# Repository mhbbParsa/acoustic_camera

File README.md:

# Acoustic Camera

https://github.com/user-attachments/assets/35040632-333c-4387-a5bf-bf2f547ff368

A real-time acoustic camera built around a 30-element MEMS microphone array and an FPGA beamformer. The FPGA extracts a single target frequency from every microphone, steers a 32×32 grid of look directions with a CORDIC-based phase rotator, and streams the resulting sound-power map out over UART to a Python viewer with either a plain live heatmap, or overlaid on a webcam feed. A physical switch flips the beamformer between a wide 180° field of view and a zoomed-in 60° view, another five switches set display gain (read back on the board's own 7-segment display), and holding spacebar in the camera overlay re-centers the heatmap on whatever's currently loudest.

Curiosity about phased array radar antennas and electronic beam steering led me to make this more accessible alternative, that replaces the difficult, expensive RF design with acoustic equivalents that are cheap to prototype and safe to probe by hand. The underlying math is identical. Only the wavelength and the hardware changed.

| | |
|---|---|
| Target frequency | 20 kHz (single-bin Goertzel) |
| Array | 30 mics, Fermat/Vogel spiral, ~90 mm diameter (measured from PCB layout) |
| Sample rates | 2 MHz PDM → 62.5 kHz decimated audio (2 MHz / 32) |
| Field of view | 60° (zoomed) or 180° (wide), switch-selectable |
| Angular resolution | ≈11° (rough λ/D estimate at 20 kHz, not a precise figure) |
| Frame rate to host | ≈60 fps (Goertzel-gated, comfortably clears the 2 Mbaud UART link) |
| FPGA | Xilinx Artix-7 `xc7a35tcpg236-1` (Digilent Basys3) |

*20 kHz source → 30-mic PCB → Pmod → Basys3 → USB → host PC live viewer.*

## How it works

```mermaid
flowchart TD
    MIC["30x SPH0641LU4H\nPDM MEMS mics"] -->|"30x 1-bit PDM"| MM["master_mic.sv\nclock gen + time-multiplexed capture"]
    MM -->|"mic_clk"| MIC
    MM -->|"30x PDM"| CIC["CIC.sv\n4th-order CIC decimation"]
    CIC -->|"30x 18-bit PCM"| GZ["goertzel.sv\nsingle-bin DFT @ target freq"]
    GZ -->|"30x (I,Q) phasors"| BF["beamformer.sv\nCORDIC delay-and-sum (cordic_0 IP)"]
    CTRL["zoom + gain switches"] --> BF
    CTRL --> DD["digit_disp.sv + sevenseg.sv\n7-segment gain readout"]
    BF -->|"1024 pixels, 16-bit"| FB["framebuffer.sv\ndouble-buffered BRAM"]
    FB --> UART["UART.sv\n2 Mbaud"]
    UART --> HOST["live_heatmap.py /\ncamera_overlay.py"]
    CAM["webcam"] -->|"camera_overlay.py only"| HOST
```

1. **Acquisition** (`master_mic.sv`) — the 30 microphones are wired as 15 pairs sharing 15 physical pins; even mics are latched on one clock phase, odd mics on the other, so all 30 PDM streams are captured with one `mic_clk`.
2. **Decimation** (`CIC.sv`) — each mic's 1-bit PDM stream is decimated by a 4th-order CIC filter into signed 18-bit PCM audio.
3. **Frequency extraction** (`goertzel.sv`) — a single-bin Goertzel filter (default target: 20 kHz) runs per microphone, producing the real/imaginary component of that mic's signal at the target frequency.
4. **Beamforming** (`beamformer.sv`) — for each of 1024 steering directions (a 32×32 `(u,v)` grid), a Xilinx CORDIC IP core (`cordic_0`) rotates every microphone's phasor by the phase delay for that direction; the rotated phasors are summed and the power is written into the corresponding pixel of a double-buffered block-RAM framebuffer. The **zoom switch** rescales the mic coordinates fed into this calculation, narrowing the steering grid from a 180° field of view down to 60°. The **gain switches** set how far the accumulated power is right-shifted before being stored, controlling display brightness.
5. **Readout** (`UART.sv`) — once a full 1024-pixel frame is ready, it's streamed out at 2 Mbaud (`0xAA 0x55` sync header, then each pixel as 16-bit little-endian) to a host PC.
6. **On-board readout** (`digit_disp.sv` / `sevenseg.sv`) — the current gain value is continuously multiplexed onto the board's two-digit 7-segment display, so gain can be read without a host PC attached.

`vga_controller.sv` is implemented and was tested driving a live monitor earlier in this project; it's currently unused because the framebuffer only exposes a single read port, which is now assigned to UART for host streaming (not an unfinished module).

Mic positions follow a Fermat/Vogel spiral ("sunflower" pattern) so steering delays are computed from fixed-point `(X, Y)` coordinates baked into `beamformer.sv` at synthesis time.

## Design decisions

- **Double buffering, not a single shared framebuffer.** `framebuffer.sv` ping-pongs between two block RAMs: the beamformer always writes into one while UART reads out the other, swapping only once a full frame is ready and UART has finished the previous one. This avoids ever streaming a half-written frame.
- **2 Mbaud specifically.** `CLK_HZ / BAUD = 100,000,000 / 2,000,000 = 50` exactly with an integer UART bit-clock divisor, so there's no baud-rate rounding error accumulating over a frame.
- **Retargeting the Goertzel frequency.** Changing `MIC_HZ` or `DECIMATION_FACTOR` changes the decimated audio sample rate, which shifts which physical frequency the fixed Goertzel coefficients (`COS_w`/`SIN_w`) pick out. This has been verified working down to 10 kHz. That alone does *not* rescale the beamformer's `(X, Y)` mic-position constants, though, which are baked in relative to a reference wavelength; retargeting further out requires regenerating a new coordinate set from `MATLAB/coordinates.m`.

## Live viewer (Python)

Both tools auto-detect the Basys3's UART over USB (FTDI VID:PID `0403:6010`), so no port needs to be specified.

- **`live_heatmap.py`** — a plain live heatmap window. Run it with no arguments.
- **`camera_overlay.py`** — alpha-blends the heatmap over a webcam feed (window 0) instead, with the black→blue→cyan→yellow→red gradient faded in proportionally to signal strength, so quiet regions stay transparent and only real sources light up. A one-pole temporal filter (`PERSISTENCE_DECAY`) smooths frame-to-frame noise. **Hold spacebar** to re-center the heatmap on whatever's currently loudest, correcting for the mic array not being perfectly boresighted with the camera.

```
pip install pyserial opencv-python numpy
python3 live_heatmap.py
python3 camera_overlay.py
```

## Repository layout

| Path | Contents |
|---|---|
| `FPGA/` | Vivado 2025.2 project targeting a Digilent Basys3 (`xc7a35tcpg236-1`). SystemVerilog sources live in `acoustic_camera.srcs/sources_1/new/`, testbenches in `acoustic_camera.srcs/sim_1/new/`. |
| `PCB/` | KiCad project for the 30-mic sensor board (SPH0641LU4H PDM MEMS microphones). |
| `MATLAB/` | Floating-point beamforming simulation and mic-array coordinate generation used to derive the fixed-point constants in `beamformer.sv`. |
| `pics/` | PCB photos/renders and simulated/measured beamformer output, at both FOV settings. |
| `live_heatmap.py`, `camera_overlay.py` | Live viewers for the UART pixel stream (see above). |

## FPGA modules

| Module | Role |
|---|---|
| `acoustic_camera.sv` | Top level; wires the mic front end, Goertzel bank, beamformer, framebuffer, UART, and 7-segment display together. |
| `master_mic.sv` | Mic clock generation and time-multiplexed capture of the 30 PDM lines. |
| `CIC.sv` | 4th-order CIC decimation filter, PDM → 18-bit PCM. |
| `goertzel.sv` | Per-mic single-bin DFT at the configured target frequency. |
| `beamformer.sv` | CORDIC-driven phase-domain delay-and-sum beamformer, 32×32 steering grid, switchable 60°/180° FOV and gain. |
| `framebuffer.sv` | Double-buffered (ping-pong) block-RAM frame store; the beamformer writes one buffer while UART reads out the other. |
| `UART.sv` | Streams a completed frame out at 2 Mbaud once `frame_ready` pulses. |
| `digit_disp.sv` / `sevenseg.sv` | Multiplexes the current gain value onto the board's 7-segment display. |
| `vga_controller.sv` | Reads the framebuffer and drives standard VGA timing; implemented and tested, currently unused (see above). |
| `cordic_0` | Vivado-generated CORDIC IP (phase → sin/cos), used by the beamformer. |

## On-board controls

| Control | Effect |
|---|---|
| `gain[4:0]` (5 switches) | Sets the right-shift applied to each pixel's accumulated power before storage, controls display brightness/sensitivity. Mirrored on the 7-segment display. |
| `zoom` (switch) | 1 = 60° field of view (zoomed in), 0 = 180° field of view (wide). |
| `rst` (button) | Active-low system reset. |

## Pmod wiring

The 30 PDM lines are time-multiplexed down to 15 physical pins (`data[0:14]`, one pair of mics per pin), split across two Basys3 headers. See `FPGA/acoustic_camera.srcs/constrs_1/new/acoustic_camera.xdc` for the exact pin-to-signal mapping and `PCB/` for which physical mic pair lands on each line:

| Header | Signals |
|---|---|
| Pmod JA | `data[8:14]`, `mic_clk` |
| Pmod JXADC | `data[0:7]` |

## Resource utilization

From `FPGA/acoustic_camera.runs/impl_1/` (Vivado 2025.2, `xc7a35tcpg236-1`, fully placed and routed):

| Resource | Used | Available | Utilization |
|---|---|---|---|
| Slice LUTs | 7,439 | 20,800 | 35.8% |
| Slice Registers | 11,511 | 41,600 | 27.7% |
| Block RAM (RAMB18) | 1 | 50 | 2.0% |
| DSP48E1 | 20 | 90 | 22.2% |

Timing closes at 100 MHz (the system clock constraint) with +0.179 ns worst negative slack, and all user-specified constraints met.

## Simulation

- `master_mic_tb.sv`, `beamformer_tb.sv` — unit testbenches for the mic front end and beamformer.
- `acoustic_camera_tb.sv` — drives a synthetic tone into the full pipeline and dumps the resulting frame to `framebuffer.txt`.
- `FPGA/sim_image.py` converts `framebuffer.txt` into a viewable PNG for quick visual inspection of simulation results.

## MATLAB

- `coordinates.m` — generates the Fermat-spiral microphone positions and the fixed-point `(X, Y)` constants consumed by `beamformer.sv`.
- `acoustic_camera.m` — floating-point simulation of the beamforming algorithm, used to validate steering vectors and visualize expected sound-source power maps (at both 60° and 180° FOV) before committing a design to hardware.

## Results

Three stages of validation, from the floating-point reference model down to the physical board:

**1. MATLAB (floating-point algorithm)**

| | 60° FOV | 180° FOV |
|---|---|---|
| Single source |  |  |
| Double source |  |  |

Double-source scenes are two equal-level 20 kHz sources, ~30° apart. In the 180° views, the region outside the unit circle (u²+v² > 1) is non-physical. Direction cosines beyond that boundary don't correspond to a real look angle, so ignore any energy shown in the corners.

**2. Vivado (RTL simulation)** — confirms the fixed-point SystemVerilog implementation matches the floating-point reference above:

| 60° FOV | 180° FOV |
|---|---|
|  |  |

**3. Hardware (live capture)** — via `camera_overlay.py`, at 60° FOV, same two-equal-level-sources-~30°-apart setup as above:

| Single source | Double source |
|---|---|
|  |  |

## Hardware

| PCB front (model) | PCB back (model) |
|---|---|
|  |  |

- 30x Knowles/CUI `SPH0641LU4H` PDM MEMS microphones on a Fermat-spiral array, laid out and placed programmatically via `PCB/script.py` (KiCad scripting console).
- Sensor board connects to the Basys3 over the JA and JXADC Pmod headers (see `FPGA/acoustic_camera.srcs/constrs_1/new/acoustic_camera.xdc`).
- Output is a plain UART TX line, read by a host PC's USB-serial adapter with no VGA monitor needed for normal operation.

## Getting started

- **FPGA**: open `FPGA/acoustic_camera.xpr` in Vivado 2025.2 or later (Basys3 board files required); the CORDIC IP core is regenerated automatically from `cordic_0.xci`.
- **Live viewer**: `pip install pyserial opencv-python numpy`, then run `python3 live_heatmap.py` or `python3 camera_overlay.py` (no arguments needed, both auto-detect the board over USB).
- **PCB**: open `PCB/acoustic_camera.kicad_pro` in KiCad 7+.
- **MATLAB**: run `MATLAB/acoustic_camera.m` for the beamforming simulation, or `MATLAB/coordinates.m` to regenerate the mic array layout constants.

## Status

End-to-end bring-up on hardware works: populated array → FPGA → UART → live heatmap on a host PC, with switchable FOV/gain and an optional webcam overlay. Remaining work is refinement (calibration, image quality) rather than core functionality.

## License

MIT — see [LICENSE](LICENSE).

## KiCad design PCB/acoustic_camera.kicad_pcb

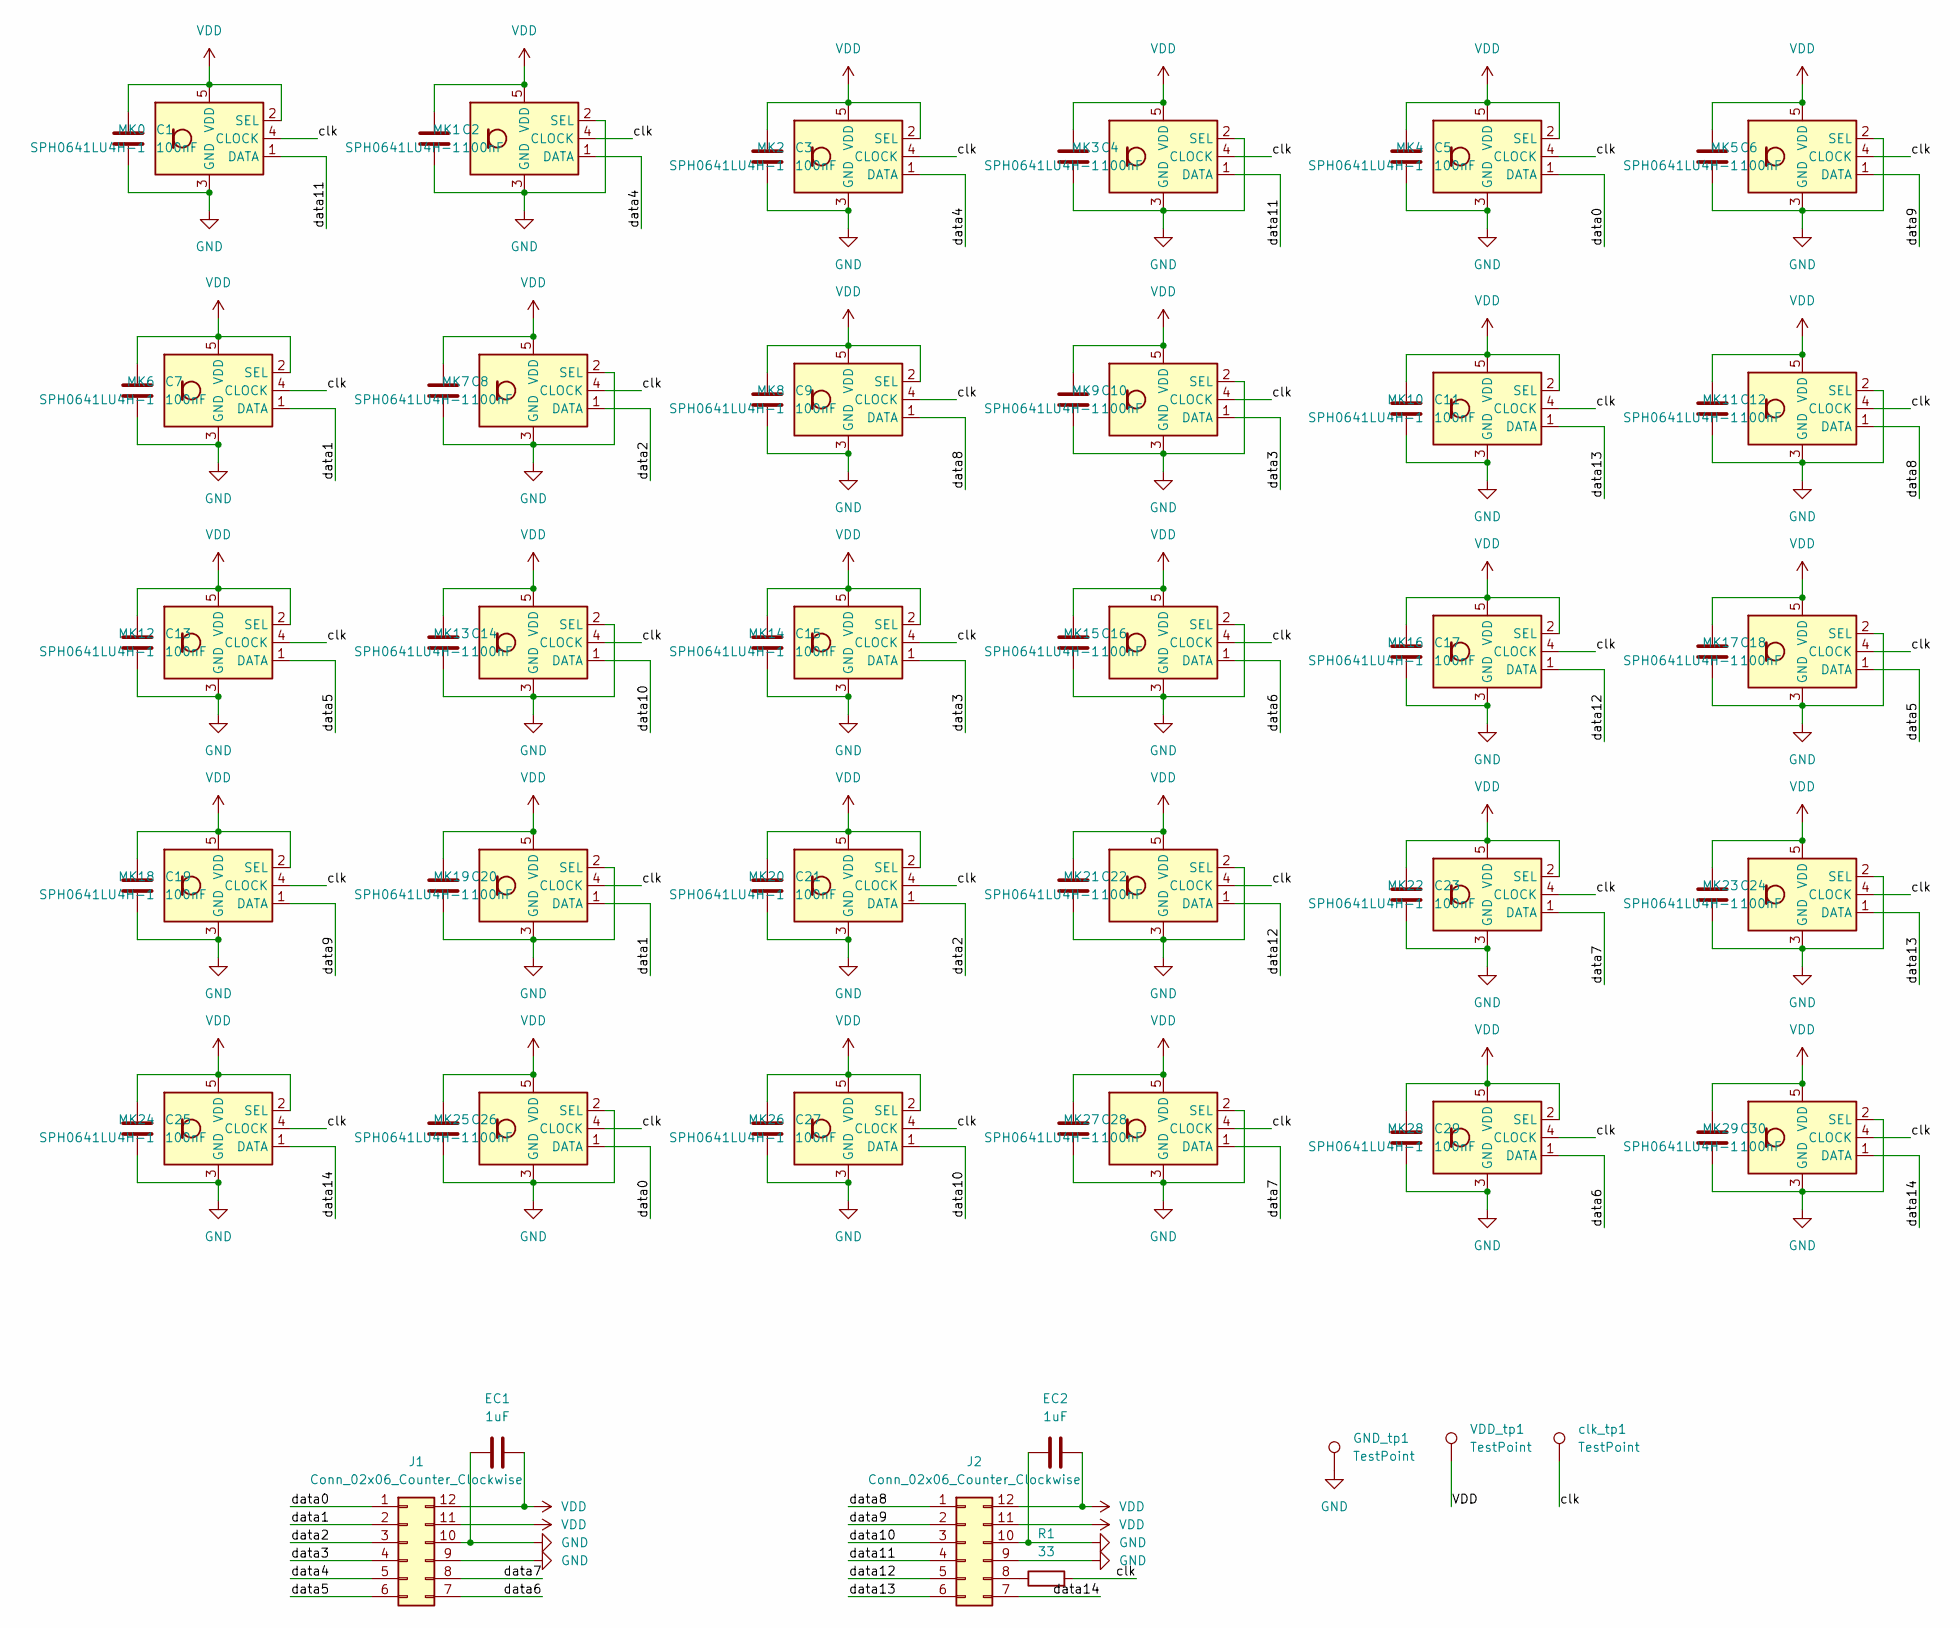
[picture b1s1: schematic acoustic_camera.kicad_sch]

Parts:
C1, C2, C3, C4, C5, C6, C7, C8, C9, C10, C11, C12, C13, C14, C15, C16, C17, C18, C19, C20, C21, C22, C23, C24, C25, C26, C27, C28, C29, C30: 100nF; C_0402_1005Metric
EC1, EC2: 1uF; C_0603_1608Metric
GND_tp1: TestPoint; TestPoint_Pad_D1.5mm
J1, J2: Conn_02x06_Counter_Clockwise; PinHeader_2x06_P2.54mm_Vertical
MK0, MK1, MK2, MK3, MK4, MK5, MK6, MK7, MK8, MK9, MK10, MK11, MK12, MK13, MK14, MK15, MK16, MK17, MK18, MK19, MK20, MK21, MK22, MK23, MK24, MK25, MK26, MK27, MK28, MK29: SPH0641LU4H-1; Knowles_LGA-5_3.5x2.65mm
R1: 33; R_0603_1608Metric
VDD_tp1: TestPoint; TestPoint_Pad_D1.5mm
clk_tp1: TestPoint; TestPoint_Pad_D1.5mm

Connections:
/clk: MK0.4 (CLOCK), MK1.4 (CLOCK), MK2.4 (CLOCK), MK3.4 (CLOCK), MK4.4 (CLOCK), MK5.4 (CLOCK), MK6.4 (CLOCK), MK7.4 (CLOCK), MK8.4 (CLOCK), MK9.4 (CLOCK), MK10.4 (CLOCK), MK11.4 (CLOCK), MK12.4 (CLOCK), MK13.4 (CLOCK), MK14.4 (CLOCK), MK15.4 (CLOCK), MK16.4 (CLOCK), MK17.4 (CLOCK), MK18.4 (CLOCK), MK19.4 (CLOCK), MK20.4 (CLOCK), MK21.4 (CLOCK), MK22.4 (CLOCK), MK23.4 (CLOCK), MK24.4 (CLOCK), MK25.4 (CLOCK), MK26.4 (CLOCK), MK27.4 (CLOCK), MK28.4 (CLOCK), MK29.4 (CLOCK), R1.2, clk_tp1.1 (1_1)
/data0: J1.1, MK4.1 (DATA), MK25.1 (DATA)
/data1: J1.2, MK6.1 (DATA), MK19.1 (DATA)
/data2: J1.3, MK7.1 (DATA), MK20.1 (DATA)
/data3: J1.4, MK9.1 (DATA), MK14.1 (DATA)
/data4: J1.5, MK1.1 (DATA), MK2.1 (DATA)
/data5: J1.6, MK12.1 (DATA), MK17.1 (DATA)
/data6: J1.7, MK15.1 (DATA), MK28.1 (DATA)
/data7: J1.8, MK22.1 (DATA), MK27.1 (DATA)
/data8: J2.1, MK8.1 (DATA), MK11.1 (DATA)
/data9: J2.2, MK5.1 (DATA), MK18.1 (DATA)
/data10: J2.3, MK13.1 (DATA), MK26.1 (DATA)
/data11: J2.4, MK0.1 (DATA), MK3.1 (DATA)
/data12: J2.5, MK16.1 (DATA), MK21.1 (DATA)
/data13: J2.6, MK10.1 (DATA), MK23.1 (DATA)
/data14: J2.7, MK24.1 (DATA), MK29.1 (DATA)
GND: C1.2, C2.2, C3.2, C4.2, C5.2, C6.2, C7.2, C8.2, C9.2, C10.2, C11.2, C12.2, C13.2, C14.2, C15.2, C16.2, C17.2, C18.2, C19.2, C20.2, C21.2, C22.2, C23.2, C24.2, C25.2, C26.2, C27.2, C28.2, C29.2, C30.2, EC1.1, EC2.1, GND_tp1.1 (1_1), J1.9, J1.10, J2.9, J2.10, MK0.3 (GND), MK1.2 (SEL), MK1.3 (GND), MK2.3 (GND), MK3.2 (SEL), MK3.3 (GND), MK4.3 (GND), MK5.2 (SEL), MK5.3 (GND), MK6.3 (GND), MK7.2 (SEL), MK7.3 (GND), MK8.3 (GND), MK9.2 (SEL), MK9.3 (GND), MK10.3 (GND), MK11.2 (SEL), MK11.3 (GND), MK12.3 (GND), MK13.2 (SEL), MK13.3 (GND), MK14.3 (GND), MK15.2 (SEL), MK15.3 (GND), MK16.3 (GND), MK17.2 (SEL), MK17.3 (GND), MK18.3 (GND), MK19.2 (SEL), MK19.3 (GND), MK20.3 (GND), MK21.2 (SEL), MK21.3 (GND), MK22.3 (GND), MK23.2 (SEL), MK23.3 (GND), MK24.3 (GND), MK25.2 (SEL), MK25.3 (GND), MK26.3 (GND), MK27.2 (SEL), MK27.3 (GND), MK28.3 (GND), MK29.2 (SEL), MK29.3 (GND)
unnamed: J2.8, R1.1
VDD: C1.1, C2.1, C3.1, C4.1, C5.1, C6.1, C7.1, C8.1, C9.1, C10.1, C11.1, C12.1, C13.1, C14.1, C15.1, C16.1, C17.1, C18.1, C19.1, C20.1, C21.1, C22.1, C23.1, C24.1, C25.1, C26.1, C27.1, C28.1, C29.1, C30.1, EC1.2, EC2.2, J1.11, J1.12, J2.11, J2.12, MK0.2 (SEL), MK0.5 (VDD), MK1.5 (VDD), MK2.2 (SEL), MK2.5 (VDD), MK3.5 (VDD), MK4.2 (SEL), MK4.5 (VDD), MK5.5 (VDD), MK6.2 (SEL), MK6.5 (VDD), MK7.5 (VDD), MK8.2 (SEL), MK8.5 (VDD), MK9.5 (VDD), MK10.2 (SEL), MK10.5 (VDD), MK11.5 (VDD), MK12.2 (SEL), MK12.5 (VDD), MK13.5 (VDD), MK14.2 (SEL), MK14.5 (VDD), MK15.5 (VDD), MK16.2 (SEL), MK16.5 (VDD), MK17.5 (VDD), MK18.2 (SEL), MK18.5 (VDD), MK19.5 (VDD), MK20.2 (SEL), MK20.5 (VDD), MK21.5 (VDD), MK22.2 (SEL), MK22.5 (VDD), MK23.5 (VDD), MK24.2 (SEL), MK24.5 (VDD), MK25.5 (VDD), MK26.2 (SEL), MK26.5 (VDD), MK27.5 (VDD), MK28.2 (SEL), MK28.5 (VDD), MK29.5 (VDD), VDD_tp1.1 (1_1)

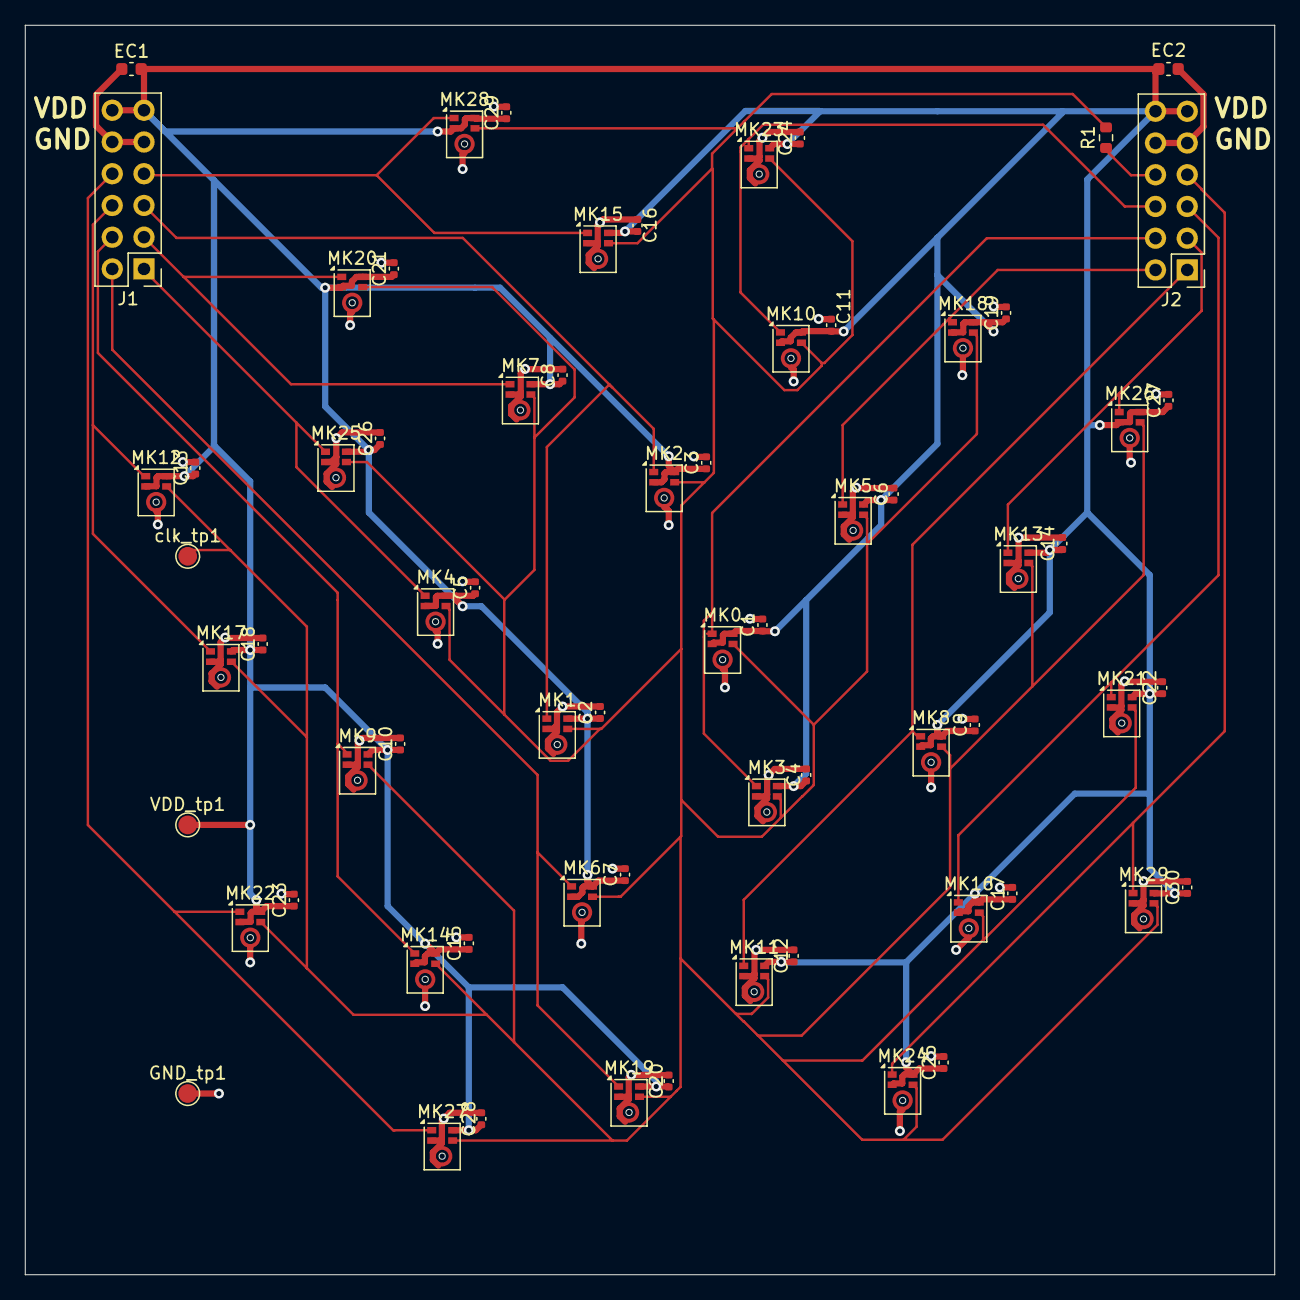
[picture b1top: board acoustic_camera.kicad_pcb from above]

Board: 2 copper layers, 100.0 x 100.0 mm, 68 parts (0 on the bottom side), 19 nets.

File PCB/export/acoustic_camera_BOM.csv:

Comment,Designator,Footprint,JLCPCB Part #
100nF,C1,C_0402_1005Metric,C1525
100nF,C2,C_0402_1005Metric,C1525
100nF,C3,C_0402_1005Metric,C1525
100nF,C4,C_0402_1005Metric,C1525
100nF,C5,C_0402_1005Metric,C1525
100nF,C6,C_0402_1005Metric,C1525
100nF,C7,C_0402_1005Metric,C1525
100nF,C8,C_0402_1005Metric,C1525
100nF,C9,C_0402_1005Metric,C1525
100nF,C10,C_0402_1005Metric,C1525
100nF,C11,C_0402_1005Metric,C1525
100nF,C12,C_0402_1005Metric,C1525
100nF,C13,C_0402_1005Metric,C1525
100nF,C14,C_0402_1005Metric,C1525
100nF,C15,C_0402_1005Metric,C1525
100nF,C16,C_0402_1005Metric,C1525
100nF,C17,C_0402_1005Metric,C1525
100nF,C18,C_0402_1005Metric,C1525
100nF,C19,C_0402_1005Metric,C1525
100nF,C20,C_0402_1005Metric,C1525
100nF,C21,C_0402_1005Metric,C1525
100nF,C22,C_0402_1005Metric,C1525
100nF,C23,C_0402_1005Metric,C1525
100nF,C24,C_0402_1005Metric,C1525
100nF,C25,C_0402_1005Metric,C1525
100nF,C26,C_0402_1005Metric,C1525
100nF,C27,C_0402_1005Metric,C1525
100nF,C28,C_0402_1005Metric,C1525
100nF,C29,C_0402_1005Metric,C1525
100nF,C30,C_0402_1005Metric,C1525
1uF,EC1,C_0603_1608Metric,C15849
1uF,EC2,C_0603_1608Metric,C15849
SPH0641LU4H-1,MK0,Knowles_LGA-5_3.5x2.65mm,C2879853
SPH0641LU4H-1,MK1,Knowles_LGA-5_3.5x2.65mm,C2879853
SPH0641LU4H-1,MK2,Knowles_LGA-5_3.5x2.65mm,C2879853
SPH0641LU4H-1,MK3,Knowles_LGA-5_3.5x2.65mm,C2879853
SPH0641LU4H-1,MK4,Knowles_LGA-5_3.5x2.65mm,C2879853
SPH0641LU4H-1,MK5,Knowles_LGA-5_3.5x2.65mm,C2879853
SPH0641LU4H-1,MK6,Knowles_LGA-5_3.5x2.65mm,C2879853
SPH0641LU4H-1,MK7,Knowles_LGA-5_3.5x2.65mm,C2879853
SPH0641LU4H-1,MK8,Knowles_LGA-5_3.5x2.65mm,C2879853
SPH0641LU4H-1,MK9,Knowles_LGA-5_3.5x2.65mm,C2879853
SPH0641LU4H-1,MK10,Knowles_LGA-5_3.5x2.65mm,C2879853
SPH0641LU4H-1,MK11,Knowles_LGA-5_3.5x2.65mm,C2879853
SPH0641LU4H-1,MK12,Knowles_LGA-5_3.5x2.65mm,C2879853
SPH0641LU4H-1,MK13,Knowles_LGA-5_3.5x2.65mm,C2879853
SPH0641LU4H-1,MK14,Knowles_LGA-5_3.5x2.65mm,C2879853
SPH0641LU4H-1,MK15,Knowles_LGA-5_3.5x2.65mm,C2879853
SPH0641LU4H-1,MK16,Knowles_LGA-5_3.5x2.65mm,C2879853
SPH0641LU4H-1,MK17,Knowles_LGA-5_3.5x2.65mm,C2879853
SPH0641LU4H-1,MK18,Knowles_LGA-5_3.5x2.65mm,C2879853
SPH0641LU4H-1,MK19,Knowles_LGA-5_3.5x2.65mm,C2879853
SPH0641LU4H-1,MK20,Knowles_LGA-5_3.5x2.65mm,C2879853
SPH0641LU4H-1,MK21,Knowles_LGA-5_3.5x2.65mm,C2879853
SPH0641LU4H-1,MK22,Knowles_LGA-5_3.5x2.65mm,C2879853
SPH0641LU4H-1,MK23,Knowles_LGA-5_3.5x2.65mm,C2879853
SPH0641LU4H-1,MK24,Knowles_LGA-5_3.5x2.65mm,C2879853
SPH0641LU4H-1,MK25,Knowles_LGA-5_3.5x2.65mm,C2879853
SPH0641LU4H-1,MK26,Knowles_LGA-5_3.5x2.65mm,C2879853
SPH0641LU4H-1,MK27,Knowles_LGA-5_3.5x2.65mm,C2879853
SPH0641LU4H-1,MK28,Knowles_LGA-5_3.5x2.65mm,C2879853
SPH0641LU4H-1,MK29,Knowles_LGA-5_3.5x2.65mm,C2879853
33,R1,R_0603_1608Metric,C177281
